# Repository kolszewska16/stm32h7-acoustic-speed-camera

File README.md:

# stm32h7-acoustic-speed-camera
Real-time acoustic event logger on STM32H723ZG. Hardware-accelerated PDM acquisition and CMSIS-DSP analysis. Features automatic event triggering with SD card logging and camera integration.

### Overview
This project is a system for monitoring and analyzing traffic noise in real-time. It doesn't just measure decibels — it "understands" the frequency spectrum and takes action. When a noise threshold is violated, the system triggers a camera and logs the event data (photo) to an SD card.

### Tech Stack & Key Features
* **MCU:** STM32H723ZG (Cortex-M7)
* **Audio:** Digital PDM MEMS microphones via **DFSDM**
* **OS:** **FreeRTOS** for multitasking
* **Storage:** **SDMMC + FatFs** for high-speed event logging

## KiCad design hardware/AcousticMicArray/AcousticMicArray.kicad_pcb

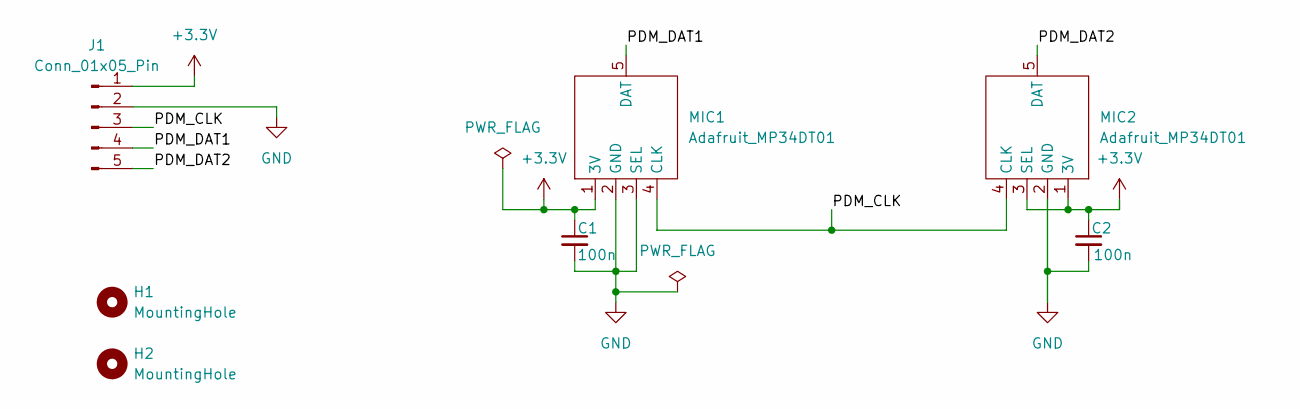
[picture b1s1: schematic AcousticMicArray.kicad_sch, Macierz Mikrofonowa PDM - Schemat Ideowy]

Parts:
C1, C2: 100n; C_0805_2012Metric_Pad1.18x1.45mm_HandSolder
H1, H2: MountingHole; MountingHole_3.2mm_M3
J1: Conn_01x05_Pin; PinHeader_1x05_P2.54mm_Vertical
MIC1, MIC2: Adafruit_MP34DT01; PinSocket_1x05_P2.54mm_Vertical

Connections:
+3.3V: C1.1, C2.1, J1.1, MIC1.1 (3V), MIC2.1 (3V), MIC2.3 (SEL)
/PDM_CLK: J1.3, MIC1.4 (CLK), MIC2.4 (CLK)
/PDM_DAT1: J1.4, MIC1.5 (DAT)
/PDM_DAT2: J1.5, MIC2.5 (DAT)
GND: C1.2, C2.2, J1.2, MIC1.2 (GND), MIC1.3 (SEL), MIC2.2 (GND)

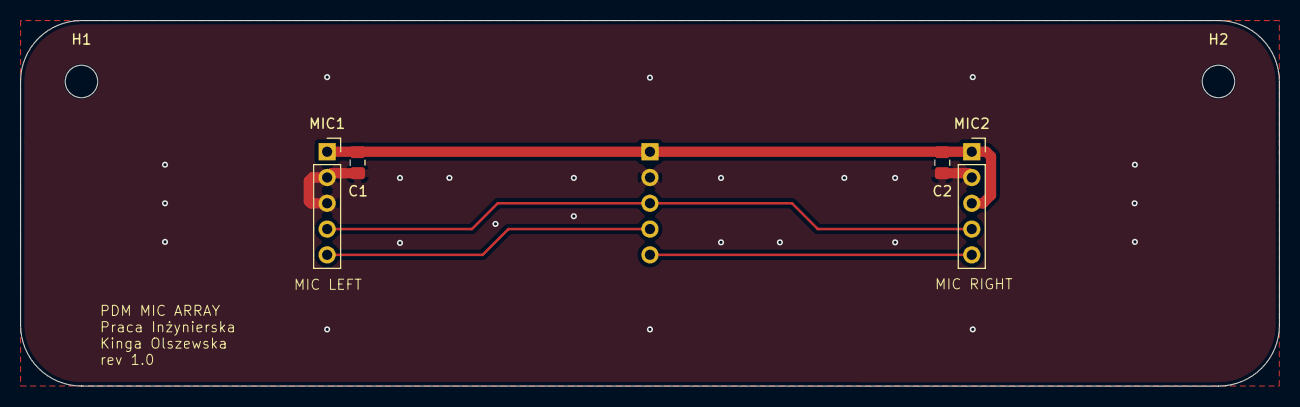
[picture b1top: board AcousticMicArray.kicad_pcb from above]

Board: 2 copper layers, 124.0 x 36.0 mm, 7 parts (1 on the bottom side), 5 nets.

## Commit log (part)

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2026-03-31 add .gitignore file
2026-03-31 implement dual-channel dBA measurement using FFT and A-weighting
2026-06-20 add dBA calibration based on microphone datasheet
